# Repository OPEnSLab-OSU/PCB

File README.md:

# Project List
Opens Staff - Clone this repo and make a folder for your PCB. Once your PCB is added, place project links and update board file links here 

## [EAGLE Library Files](https://github.com/OPEnSLab-OSU/PCB/tree/master/OPEnS_Library)
Managed Libraries Folder *Coming Soon*

<!-- Copy an existing entry and add your project links directly below this comment -->
## [Sapflow](https://github.com/OPEnSLab-OSU/OPEnS-Lab-Home/wiki/Sap-Flow-Meter)

**New* V3 Board [Sapflow](https://github.com/OPEnSLab-OSU/PCB/tree/master/Sapflow)

## [Evaporometer](https://github.com/OPEnSLab-OSU/OPEnS-Lab-Home/wiki/Evaporometer)

INA125P Load Cell Amp [DevBoard](https://github.com/OPEnSLab-OSU/PCB/tree/master/Evaporometer_Lite/INA125P)

**New* Evaporometer V2 [V2.2 Board](https://github.com/OPEnSLab-OSU/PCB/tree/master/Evaporometer_Lite)

## [Hypnos](https://github.com/OPEnSLab-OSU/OPEnS-Hypnos)

**New* V3 Board [Hypnos 12V](https://github.com/OPEnSLab-OSU/PCB/tree/master/Hypnos)

## [PNNL Flux Tool](https://github.com/OPEnSLab-OSU/PNNLFluxV1)

Head [board](https://github.com/OPEnSLab-OSU/PCB/blob/master/PNNLFlux/Head-Board/head-board.brd),
[schematic](https://github.com/OPEnSLab-OSU/PCB/blob/master/PNNLFlux/Head-Board/head-board.sch)

Rod [board](https://github.com/OPEnSLab-OSU/PCB/blob/master/PNNLFlux/Rod-Board/rod-board.brd),
[schematic](https://github.com/OPEnSLab-OSU/PCB/blob/master/PNNLFlux/Rod-Board/rod-board.sch)

MS580302 [Pressure/EC sensor](https://github.com/OPEnSLab-OSU/PCB/tree/master/PNNLFlux/MS5803-02BA)

## [SmartRock](https://github.com/OPEnSLab-OSU/SmartRock)

MS580302 Pressure [MS5803](https://github.com/OPEnSLab-OSU/PCB/tree/master/SmartRock/MS5803), 
HydroPCB [HydroPCB](https://github.com/OPEnSLab-OSU/PCB/tree/master/SmartRock/HydroPCB)

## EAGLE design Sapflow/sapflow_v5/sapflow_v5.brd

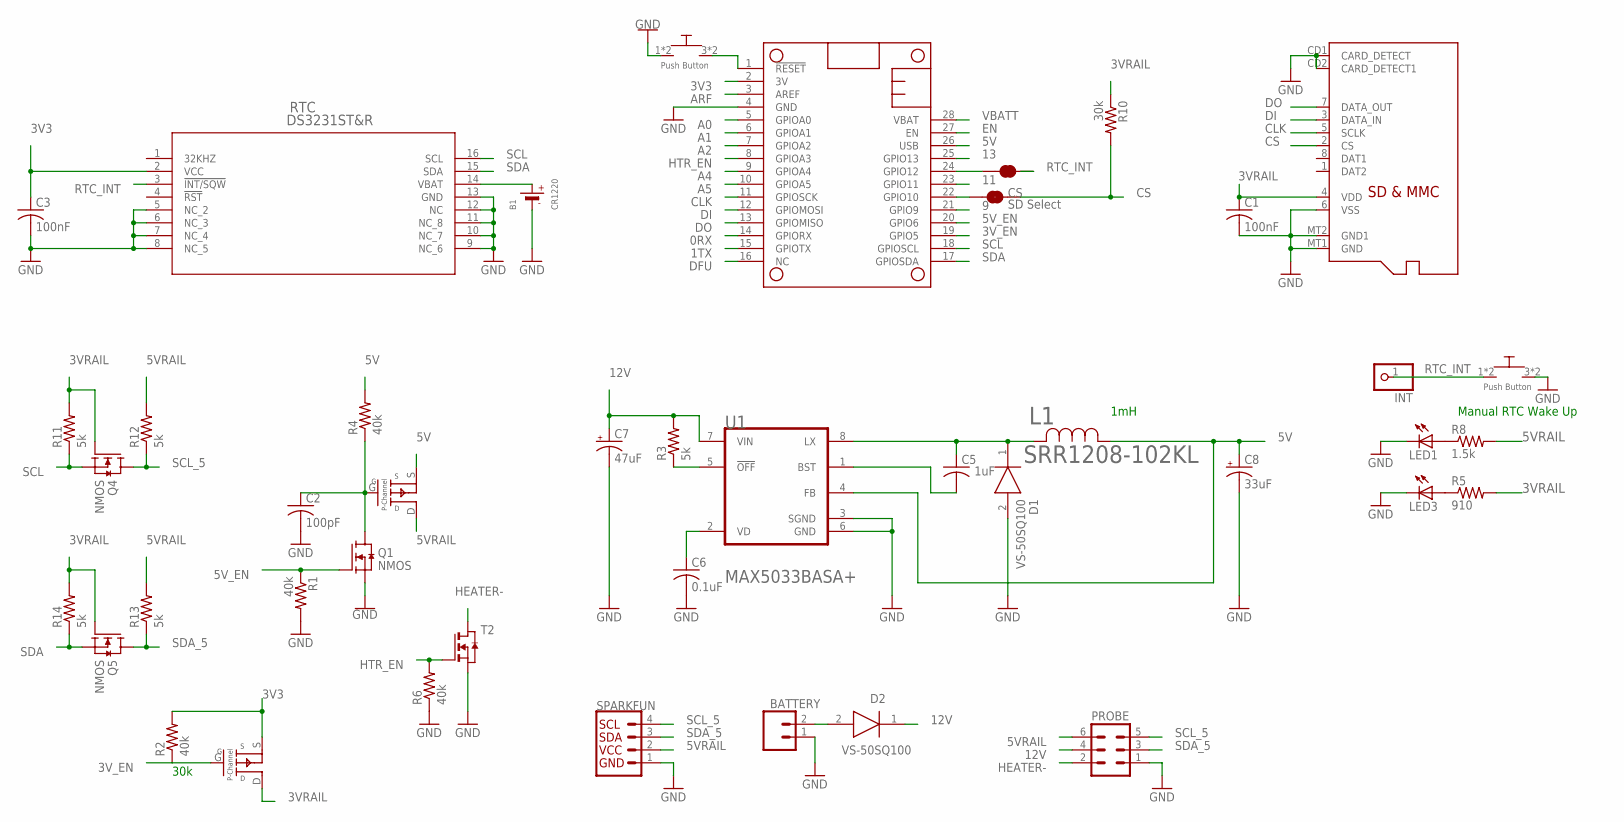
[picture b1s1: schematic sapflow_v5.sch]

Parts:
B1: CR1220
BATTERY: HIGHV-OUT; 1X02_NO_SILK
C1, C3: 100nF; C0805
C2: 100pF; C0805
C5: 1uF; C0805
C6: 0.1uF; C0805
C7: 47uF; D/7343-31R
C8: 33uF; D/7343-31R
CS: SD Select; SMT-JUMPER_2_NC_TRACE_SILK
D1, D2: VS-50SQ100; DIOAD1405W86L465D235
INT: PINHD-1X1CB; 1X01-CLEANBIG
L1: SRR1208-102KL; IND_BOURNS_SRR1208
LED1, LED3: RED; CHIPLED_0805
MICROSD: MICROSD
MS2: FEATHERWING
PMOS1, PMOS2: SSM3J3228R; SOT-23-3
PROBE: MA03-2
Q1, Q4, Q5: NMOS; SOT23-S
R1, R2, R4, R6: 40k; R0805
R3, R11, R12, R13, R14: 5k; R0805
R5: 910; R0805
R8: 1.5k; R0805
R10: 30k; R0805
RTC: DS3231ST&R; 21-0042B_16
RTC_INT: JUMPER-SMT_2_NC_TRACE_SILK; SMT-JUMPER_2_NC_TRACE_SILK
SPARKFUN: I2C_STANDARD_NO_SILK; 1X04_NO_SILK
T2: NMOSSOT223; SOT223
U1: MAXIM_MAX5033BASA+MAXIM_MAX5033BASA+_0_1; MAXIM_MAX5033BASA+_1
U$1, U$2: PUSH_BUTTON; PUSHBUTTON_SMD

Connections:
0RX: MS2.14 (GPIORX)
1TX: MS2.15 (GPIOTX)
3V3: C3.1, MS2.2 (3V), PMOS2.S, R2.2, RTC.2 (VCC)
3VRAIL: C1.1, MICROSD.4 (VDD), PMOS2.D, Q4.1 (G), Q5.1 (G), R5.2, R10.1, R11.2, R14.2
3V_EN: MS2.19 (GPIO5), PMOS2.G, R2.1
5V: C8.+, L1.1, MS2.26 (USB), PMOS1.S, R4.2, U1.4 (FB)
5VRAIL: PMOS1.D, PROBE.6, R8.2, R12.2, R13.2, SPARKFUN.2 (VCC)
5V_EN: MS2.20 (GPIO6), Q1.1 (G), R1.1
9: MS2.21 (GPIO9)
11: MS2.23 (GPIO11)
12V: C7.+, D2.1 (K), PROBE.4, R3.2, U1.7 (VIN)
13: MS2.25 (GPIO13)
A0: MS2.5 (GPIOA0)
A1: MS2.6 (GPIOA1)
A2: MS2.7 (GPIOA2)
A4: MS2.9 (GPIOA4)
A5: MS2.10 (GPIOA5)
ARF: MS2.3 (AREF)
CLK: MICROSD.5 (SCLK), MS2.11 (GPIOSCK)
CS: CS.2, MICROSD.2 (CS), R10.2
DFU: MS2.16 (NC)
DI: MICROSD.3 (DATA_IN), MS2.12 (GPIOMOSI)
DO: MICROSD.7 (DATA_OUT), MS2.13 (GPIOMISO)
EN: MS2.27 (EN)
GND: B1.-, BATTERY.1, C1.2, C2.2, C3.2, C6.2, C7.-, C8.-, D1.2 (A), LED1.C, LED3.C, MICROSD.6 (VSS), MICROSD.CD1 (CARD_DETECT), MICROSD.CD2 (CARD_DETECT1), MICROSD.MT1 (GND), MICROSD.MT2 (GND1), MS2.4 (GND), PROBE.1, Q1.2 (S), R1.2, R6.1, RTC.5 (NC_2), RTC.6 (NC_3), RTC.7 (NC_4), RTC.8 (NC_5), RTC.9 (NC_6), RTC.10 (NC_7), RTC.11 (NC_8), RTC.12 (NC), RTC.13 (GND), SPARKFUN.1 (GND), T2.3 (S), U1.3 (SGND), U1.6 (GND), U$1.1, U$1.2, U$2.3, U$2.4
HEATER-: PROBE.2, T2.2 (D), T2.4 (D)
HTR_EN: MS2.8 (GPIOA3), R6.2, T2.1 (G)
unnamed: MS2.1 (!RESET), U$1.3, U$1.4
unnamed: B1.+$1 (+), RTC.14 (VBAT)
unnamed: BATTERY.2, D2.2 (A)
unnamed: LED3.A, R5.1
unnamed: C6.1, U1.2 (VD)
unnamed: R3.1, U1.5 (!OFF!)
unnamed: C2.1, PMOS1.G, Q1.3 (D), R4.1
unnamed: CS.1, MS2.22 (GPIO10)
unnamed: LED1.A, R8.1
unnamed: MS2.24 (GPIO12), RTC_INT.1
unnamed: C5.2, U1.1 (BST)
unnamed: C5.1, D1.1 (K), L1.2, U1.8 (LX)
RTC_INT: INT.1, RTC.3 (!INT/SQW), RTC_INT.2, U$2.1, U$2.2
SCL: MS2.18 (GPIOSCL), Q4.2 (S), R11.1, RTC.16 (SCL)
SCL_5: PROBE.5, Q4.3 (D), R12.1, SPARKFUN.4 (SCL)
SDA: MS2.17 (GPIOSDA), Q5.2 (S), R14.1, RTC.15 (SDA)
SDA_5: PROBE.3, Q5.3 (D), R13.1, SPARKFUN.3 (SDA)
VBATT: MS2.28 (VBAT)

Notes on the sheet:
Manual RTC Wake Up
30k
1mH

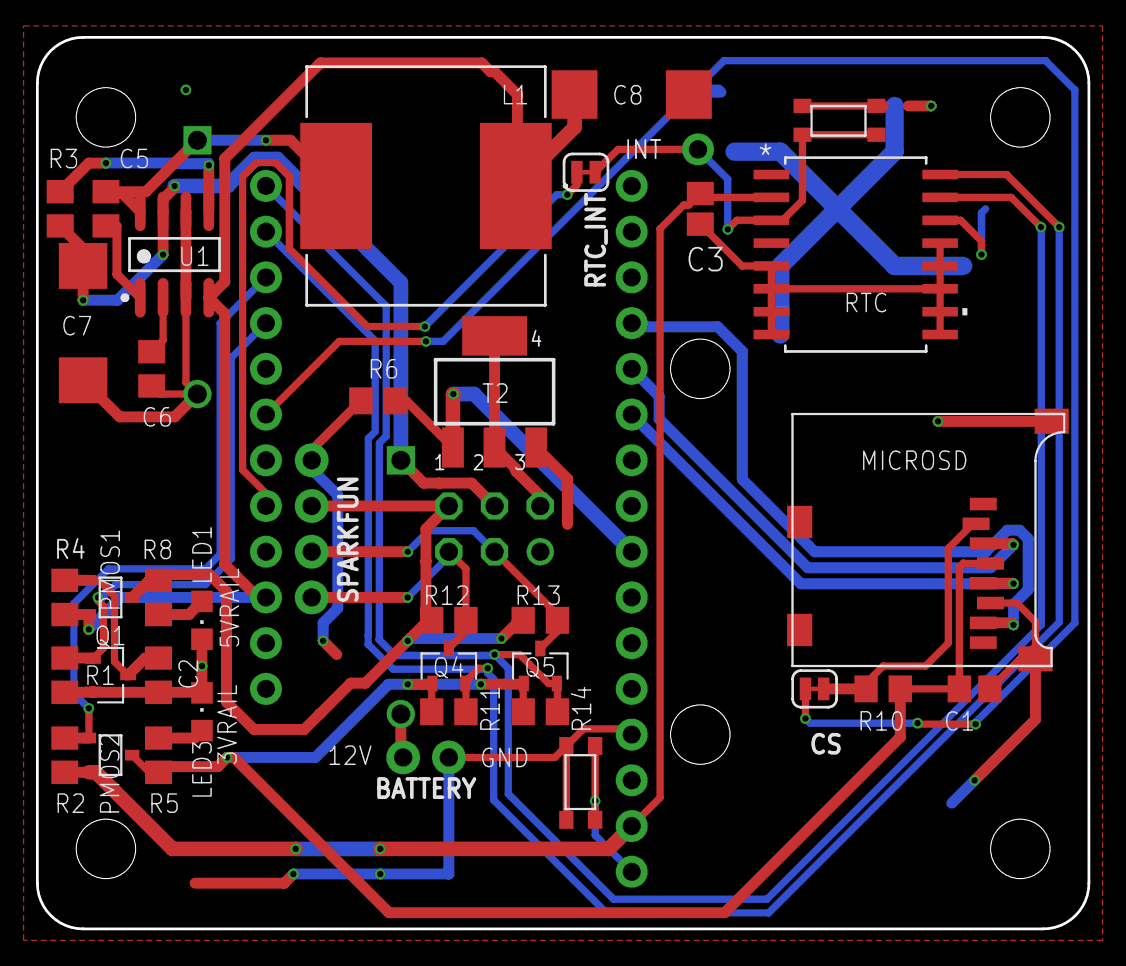
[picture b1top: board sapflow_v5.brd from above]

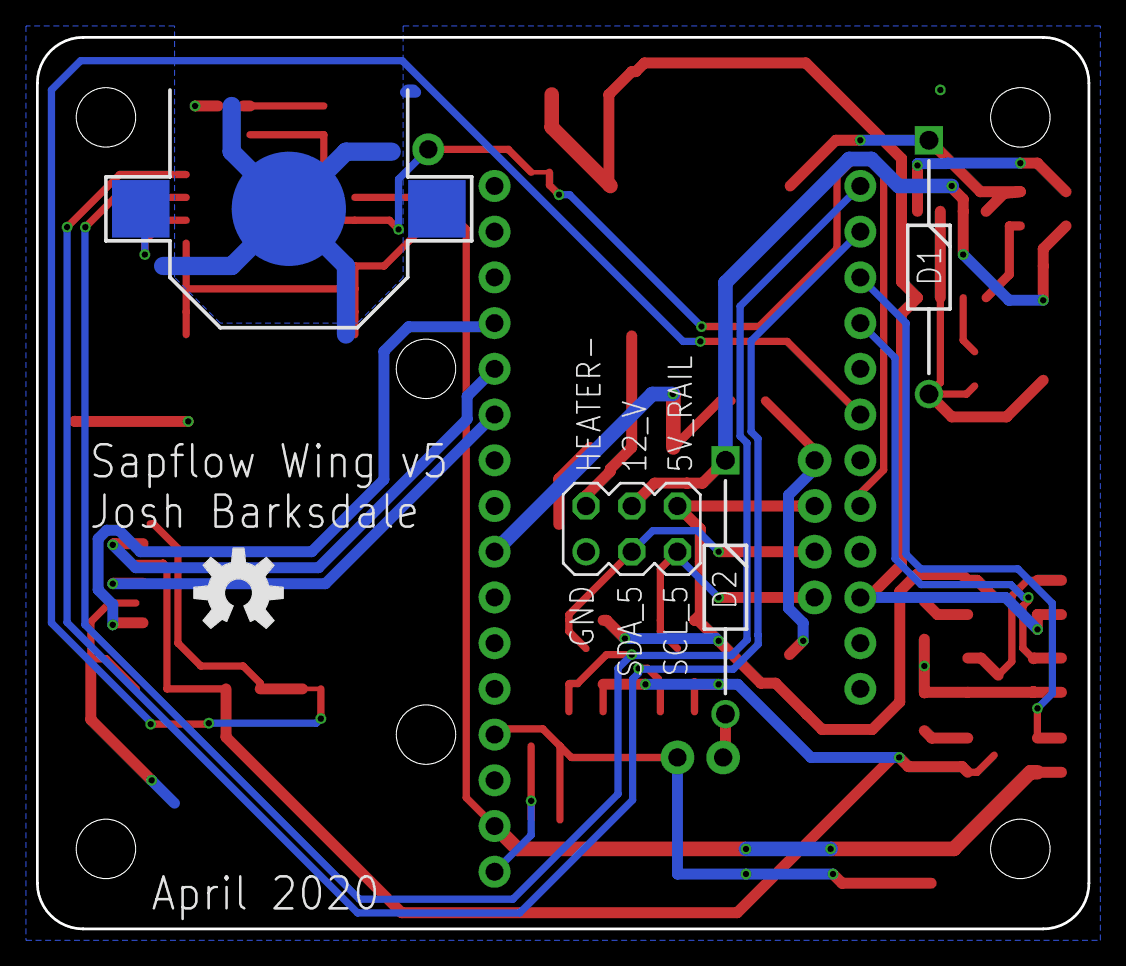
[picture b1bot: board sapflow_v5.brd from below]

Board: 2 copper layers, 58.4 x 49.5 mm, 50 parts (5 on the bottom side), 31 nets.

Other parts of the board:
H2, H4, H5, H6, H7, H8: STAND-OFF
LOGO1: OSHW-LOGOM; OSHW-LOGO-M

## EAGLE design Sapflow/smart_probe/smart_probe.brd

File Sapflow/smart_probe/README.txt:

This PCB attatches to the Sapflow project probe and makes it "smart".
It has a 3-channel ADC with analog lowpass filters in front of the inputs. 
It also has a differential I2C driver chip which can send I2C data from
the ADC over CAT V cables a couple meters long.

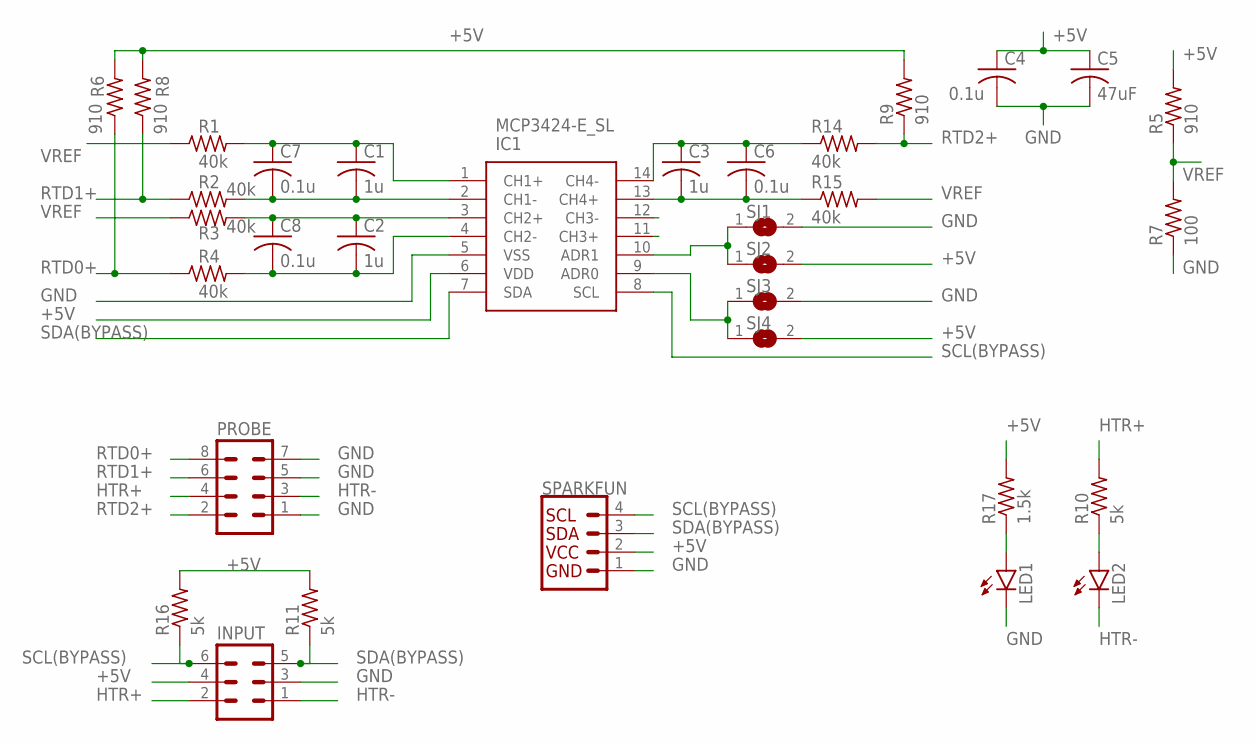
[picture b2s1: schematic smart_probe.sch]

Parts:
C1, C2, C3: 1u; C0805
C4, C6, C7, C8: 0.1u; C0805
C5: 47uF; C0805
IC1: MCP3424-E_SL; SOIC127P600X175-14N
INPUT: MA03-2
LED1, LED2: LEDCHIP-LED0805; CHIP-LED0805
PROBE: MA04-2
R1, R2, R3, R4, R14, R15: 40k; R0805
R5, R6, R8, R9: 910; R0805
R7: 100; R0805
R10, R11, R16: 5k; R0805
R17: 1.5k; R0805
SJ1, SJ2, SJ3, SJ4: SJ
SPARKFUN: I2C_STANDARD_NO_SILK; 1X04_NO_SILK

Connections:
+5V: C4.1, C5.1, IC1.6 (VDD), INPUT.4, R5.2, R6.2, R8.2, R9.2, R11.2, R16.2, R17.2, SJ2.2, SJ4.2, SPARKFUN.2 (VCC)
CH1+: C1.1, C7.1, IC1.1 (CH1+), R1.2
CH1-: C1.2, C7.2, IC1.2 (CH1-), R2.2
CH2+: C2.1, C8.1, IC1.3 (CH2+), R3.2
CH2-: C2.2, C8.2, IC1.4 (CH2-), R4.2
CH3+: IC1.11 (CH3+)
CH3-: IC1.12 (CH3-)
CH4+: C3.2, C6.2, IC1.13 (CH4+), R15.1
CH4-: C3.1, C6.1, IC1.14 (CH4-), R14.1
GND: C4.2, C5.2, IC1.5 (VSS), INPUT.3, LED1.C, PROBE.1, PROBE.5, PROBE.7, R7.1, SJ1.2, SJ3.2, SPARKFUN.1 (GND)
HTR+: INPUT.2, PROBE.4, R10.2
HTR-: INPUT.1, LED2.C, PROBE.3
unnamed: LED1.A, R17.1
unnamed: LED2.A, R10.1
unnamed: IC1.10 (ADR1), SJ1.1, SJ2.1
unnamed: IC1.9 (ADR0), SJ3.1, SJ4.1
RTD0+: PROBE.8, R4.1, R6.1
RTD1+: PROBE.6, R2.1, R8.1
RTD2+: PROBE.2, R9.1, R14.2
SCL(BYPASS): IC1.8 (SCL), INPUT.6, R16.1, SPARKFUN.4 (SCL)
SDA(BYPASS): IC1.7 (SDA), INPUT.5, R11.1, SPARKFUN.3 (SDA)
VREF: R1.1, R3.1, R5.1, R7.2, R15.2

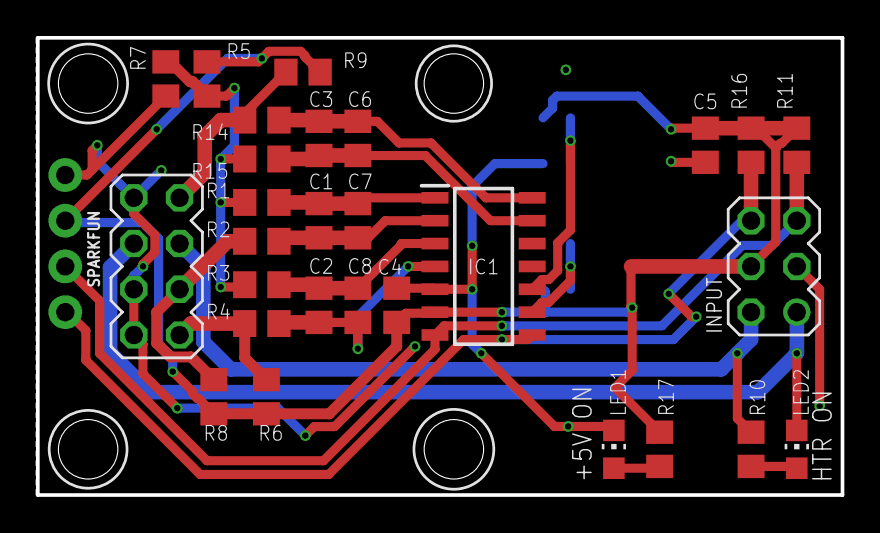
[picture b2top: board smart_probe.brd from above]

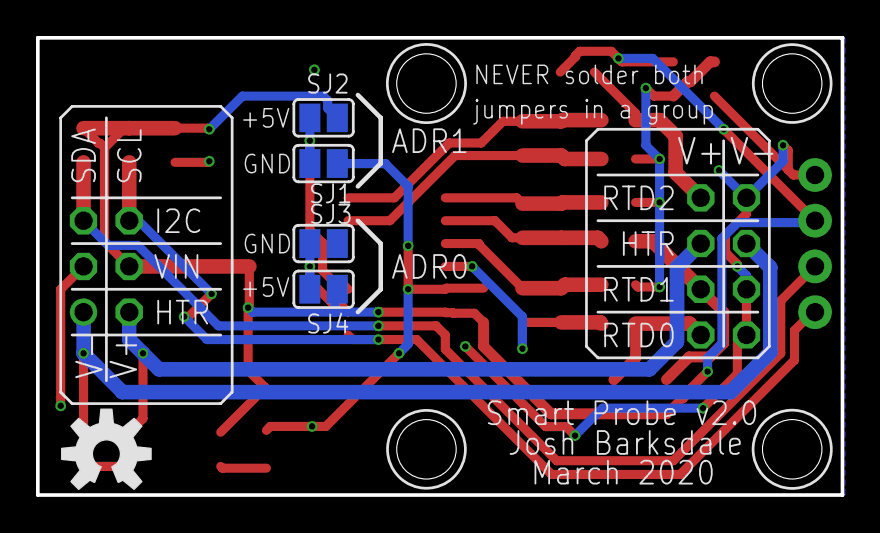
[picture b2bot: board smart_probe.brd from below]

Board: 2 copper layers, 44.7 x 25.4 mm, 38 parts (5 on the bottom side), 20 nets.

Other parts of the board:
H1, H2, H3, H4: STAND-OFF
LOGO1: OSHW-LOGOM; OSHW-LOGO-M

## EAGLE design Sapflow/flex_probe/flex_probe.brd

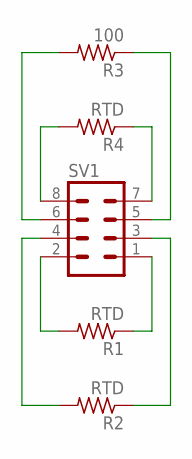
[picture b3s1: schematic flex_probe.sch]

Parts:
R1, R2, R4: RTD; R0603
R3: 100; R0603
SV1: MA04-2

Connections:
unnamed: R1.2, SV1.2
unnamed: R1.1, SV1.1
unnamed: R2.2, SV1.4
unnamed: R2.1, SV1.3
unnamed: R4.1, SV1.7
unnamed: R3.2, SV1.6
unnamed: R3.1, SV1.5
unnamed: R4.2, SV1.8

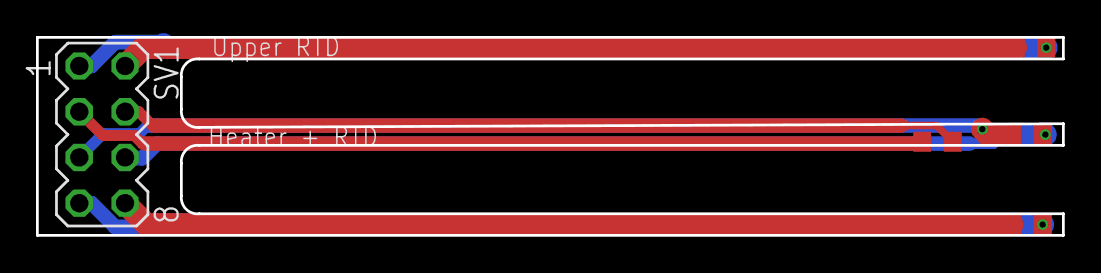
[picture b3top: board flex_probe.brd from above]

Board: 2 copper layers, 57.0 x 11.0 mm, 5 parts (0 on the bottom side), 8 nets.

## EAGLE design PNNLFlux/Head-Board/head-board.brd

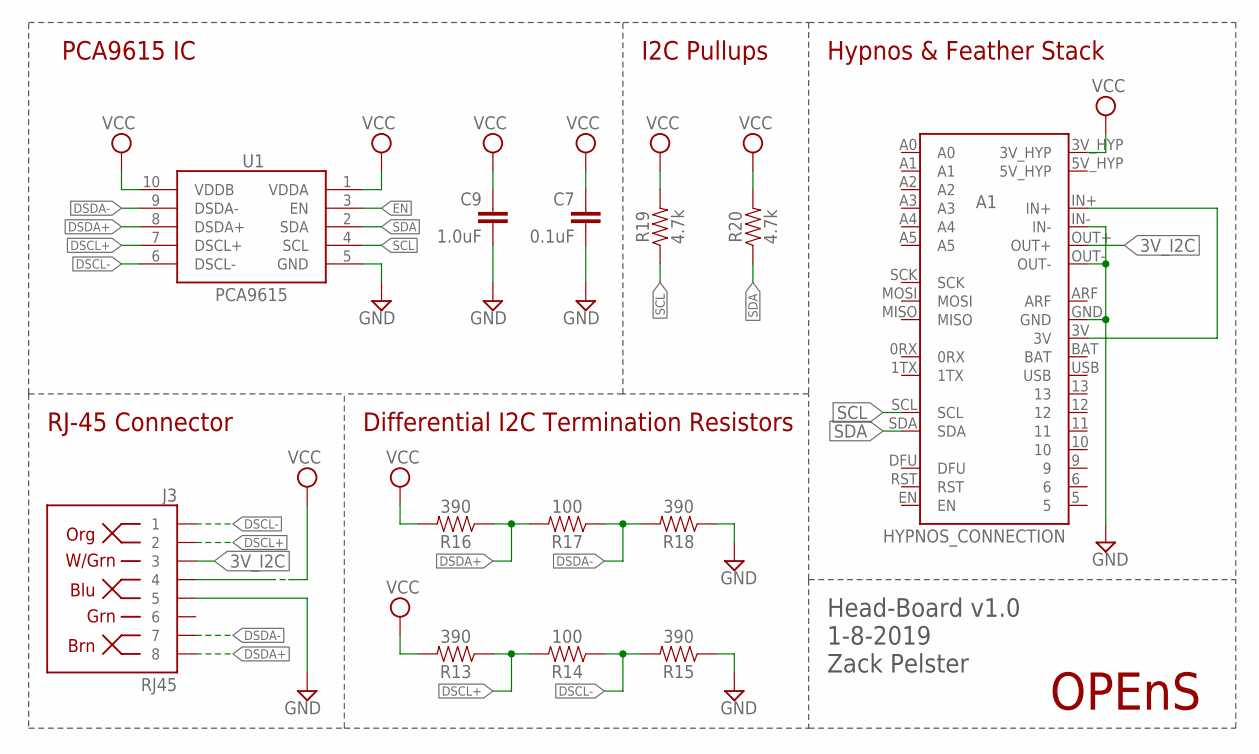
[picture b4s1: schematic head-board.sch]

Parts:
A1: HYPNOS_CONNECTION
C7: 0.1uF; 0603
C9: 1.0uF; 0603
J3: RJ45; RJ45-8
R13, R15, R16, R18: 390; 0603
R14, R17: 100; 0603
R19, R20: 4.7k; 0603
U1: PCA9615; TSSOP10
U$1: OPENS-LOGO

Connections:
3V_I2C: A1.OUT+, J3.3
BAT: A1.BAT
DSCL+: J3.2, R13.1, R14.2, U1.7 (DSCL+)
DSCL-: J3.1, R14.1, R15.2, U1.6 (DSCL-)
DSDA+: J3.8, R16.1, R17.2, U1.8 (DSDA+)
DSDA-: J3.7, R17.1, R18.2, U1.9 (DSDA-)
EN: U1.3 (EN)
GND: A1.GND, A1.IN-, A1.OUT-, C7.2, C9.2, J3.5, R15.1, R18.1, U1.5 (GND)
unnamed: A1.3V, A1.IN+
SCL: A1.SCL, R19.1, U1.4 (SCL)
SDA: A1.SDA, R20.1, U1.2 (SDA)
USB: A1.USB
VCC: A1.3V_HYP, C7.1, C9.1, J3.4, R13.2, R16.2, R19.2, R20.2, U1.1 (VDDA), U1.10 (VDDB)

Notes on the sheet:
PCA9615 IC
I2C Pullups
RJ-45 Connector
Differential I2C Termination Resistors
Head-Board v1.0 1-8-2019 Zack Pelster
Hypnos & Feather Stack

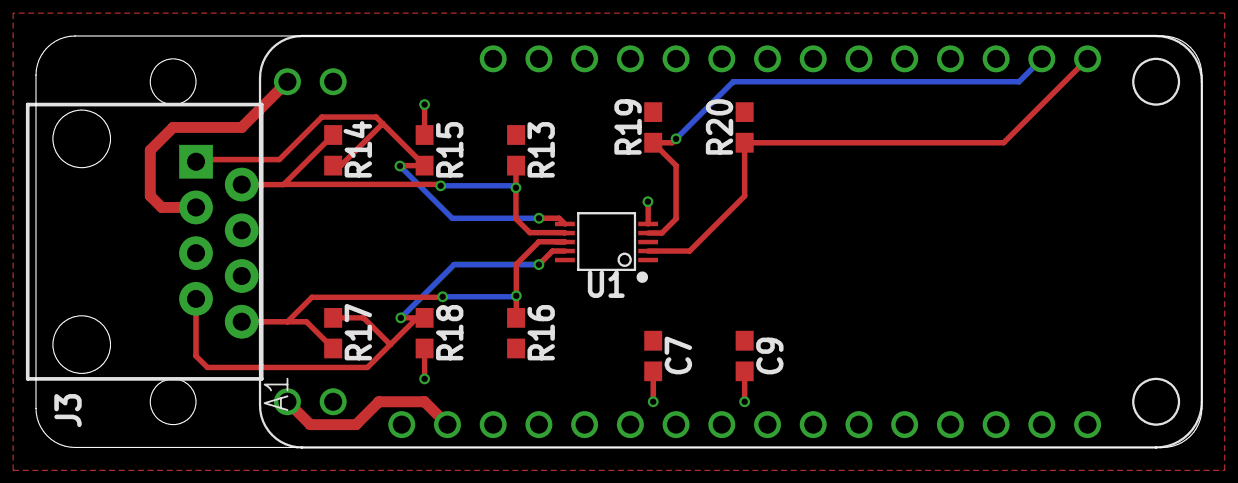
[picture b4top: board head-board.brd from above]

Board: 2 copper layers, 64.8 x 22.9 mm, 14 parts (1 on the bottom side), 10 nets.

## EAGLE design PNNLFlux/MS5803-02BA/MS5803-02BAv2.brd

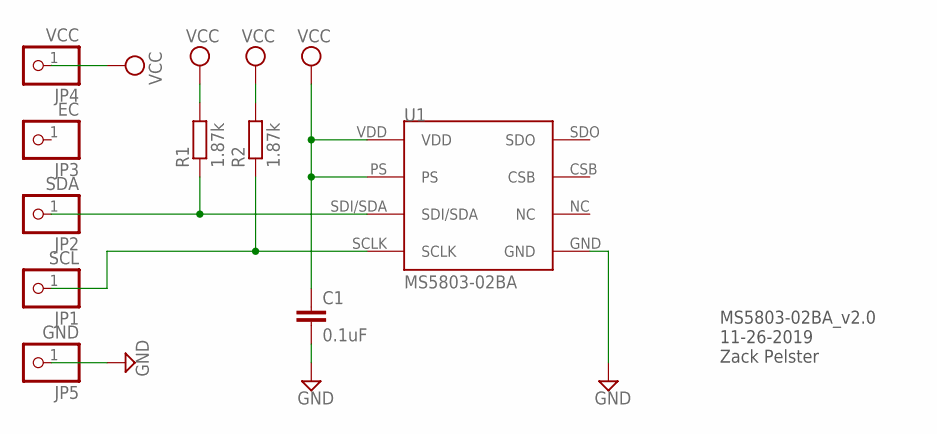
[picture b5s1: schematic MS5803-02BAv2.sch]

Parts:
C1: 0.1uF; C0805
JP1: SCL; 1X01
JP2: SDA; 1X01
JP3: EC; 1X01
JP4: VCC; 1X01
JP5: GND; 1X01
R1, R2: 1.87k; R0805
U1: MS5803-02BA

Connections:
GND: C1.2, JP5.1, U1.GND
unnamed: JP2.1, R1.1, U1.SDI/SDA
unnamed: JP1.1, R2.1, U1.SCLK
VCC: C1.1, JP4.1, R1.2, R2.2, U1.PS, U1.VDD

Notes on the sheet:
MS5803-02BA_v2.0 11-26-2019 Zack Pelster

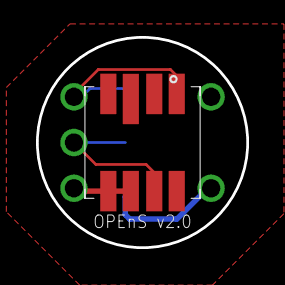
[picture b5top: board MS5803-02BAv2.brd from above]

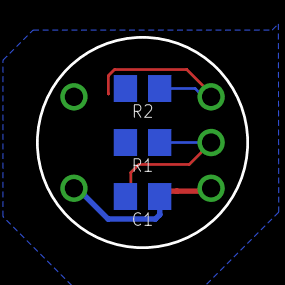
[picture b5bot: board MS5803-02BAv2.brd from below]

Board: 2 copper layers, 11.7 x 11.7 mm, 9 parts (3 on the bottom side), 4 nets.

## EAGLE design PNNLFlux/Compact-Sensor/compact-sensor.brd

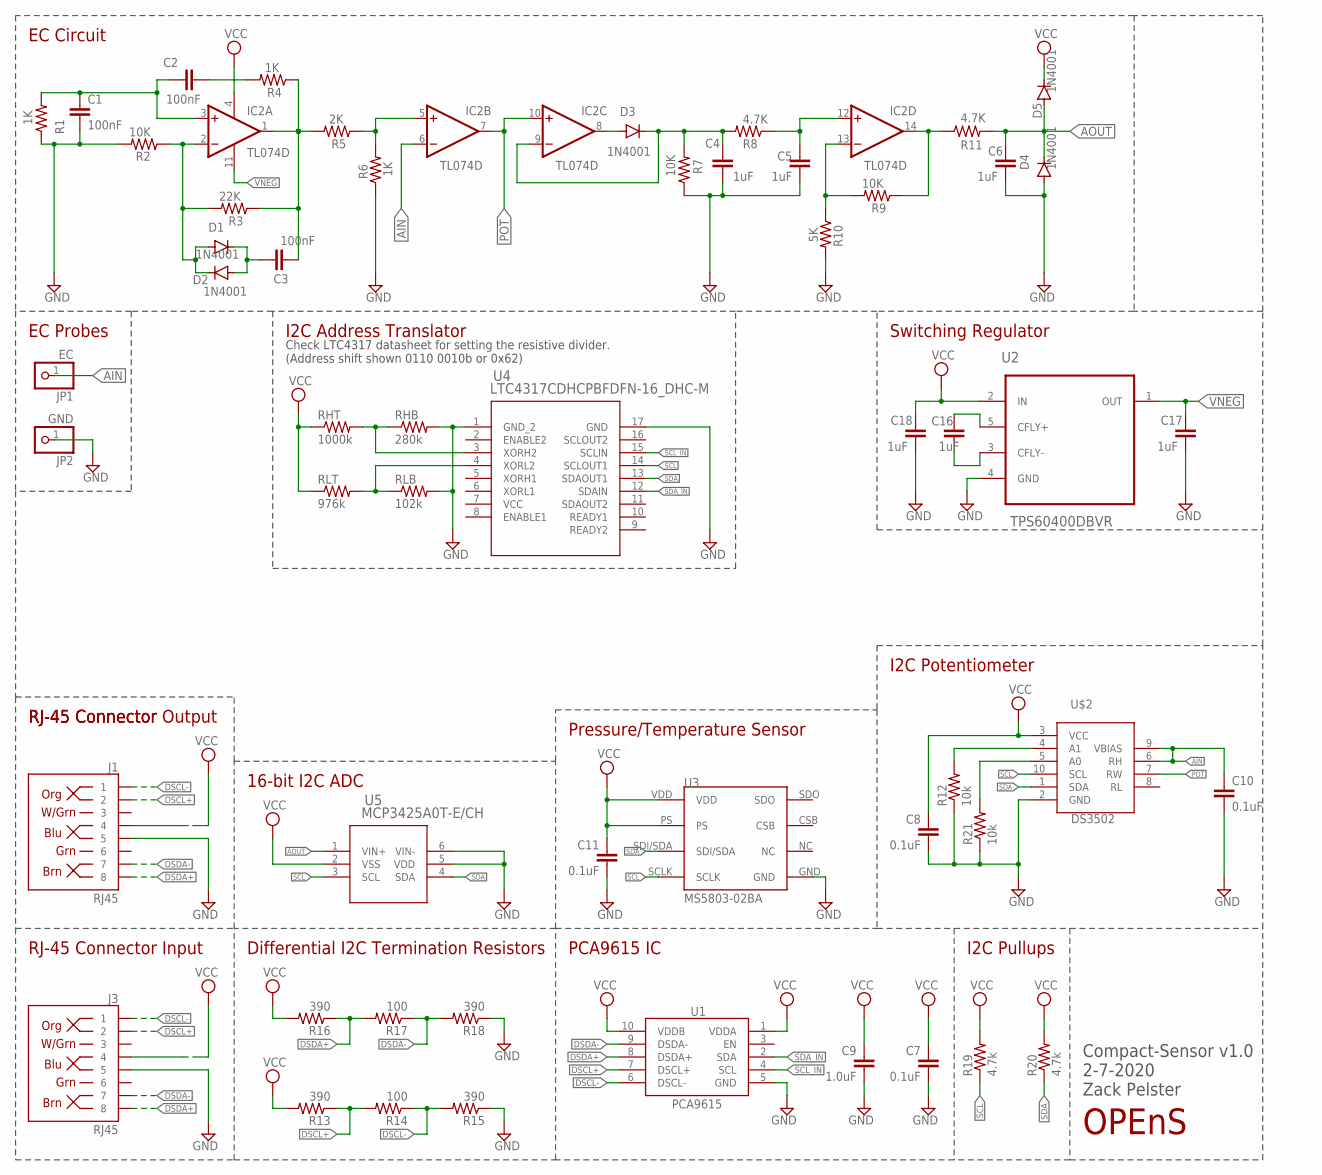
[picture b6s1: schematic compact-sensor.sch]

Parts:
C1, C2, C3: 100nF; C0603
C4, C5, C6, C16, C17, C18: 1uF; C0603
C7, C8, C10, C11: 0.1uF; C0603
C9: 1.0uF; C0603
D1, D2, D3, D4, D5: 1N4001; SOD123
IC2: TL074D; SO14
J1, J3: RJ45; RJ45-8
JP1: EC; 1X01
JP2: GND; 1X01
R1, R4, R6: 1K; R0603
R2, R7, R9: 10K; R0603
R3: 22K; R0603
R5: 2K; R0603
R8, R11: 4.7K; R0603
R10: 5K; R0603
R12, R21: 10k; R0603
R13, R15, R16, R18: 390; R0603
R14, R17: 100; R0603
R19, R20: 4.7k; R0603
RHB: 280k; R0603
RHT: 1000k; R0603
RLB: 102k; R0603
RLT: 976k; R0603
U1: PCA9615; TSSOP10
U2: TPS60400DBVR; SOT95P280X145-5N
U3: MS5803-02BA
U4: LTC4317CDHCPBFDFN-16_DHC-M; DFN-16_DHC-M
U5: MCP3425A0T-E/CH; SOT-23-6_MC
U$1: OPENS-LOGO
U$2: DS3502; MSOP10

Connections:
AIN: C10.1, IC2.6 (-IN), JP1.1, U$2.6 (RH), U$2.9 (VBIAS)
AOUT: C6.2, D4.C, D5.A, R11.2, U5.1 (VIN+)
DSCL+: J1.2, J3.2, R13.1, R14.2, U1.7 (DSCL+)
DSCL-: J1.1, J3.1, R14.1, R15.2, U1.6 (DSCL-)
DSDA+: J1.8, J3.8, R16.1, R17.2, U1.8 (DSDA+)
DSDA-: J1.7, J3.7, R17.1, R18.2, U1.9 (DSDA-)
GND: C1.2, C4.1, C5.1, C6.1, C7.2, C8.2, C9.2, C10.2, C11.2, C17.1, C18.1, D4.A, J1.5, J3.5, JP2.1, R1.1, R2.2, R6.1, R7.1, R10.2, R12.1, R15.1, R18.1, R21.1, RHB.2, RLB.2, U1.5 (GND), U2.4 (GND), U3.GND, U4.1 (GND_2), U4.17 (GND), U5.5 (VDD), U5.6 (VIN-), U$2.2 (GND)
unnamed: C1.1, C2.1, IC2.3 (+IN), R1.2
unnamed: C2.2, R4.2
unnamed: C3.2, IC2.1 (OUT), R3.1, R4.1, R5.2
unnamed: D1.A, D2.C, IC2.2 (-IN), R2.1, R3.2
unnamed: IC2.5 (+IN), R5.1, R6.2
unnamed: R12.2, U$2.4 (A1)
unnamed: R21.2, U$2.5 (A0)
unnamed: C3.1, D1.C, D2.A
unnamed: RHB.1, RHT.2, U4.3 (XORH2)
unnamed: C4.2, D3.C, IC2.9 (-IN), R7.2, R8.2
unnamed: D3.A, IC2.8 (OUT)
unnamed: C5.2, IC2.12 (+IN), R8.1
unnamed: IC2.13 (-IN), R9.2, R10.1
unnamed: RLB.1, RLT.2, U4.4 (XORL2)
unnamed: IC2.14 (OUT), R9.1, R11.1
unnamed: C16.2, U2.5 (CFLY+)
unnamed: C16.1, U2.3 (CFLY-)
POT: IC2.7 (OUT), IC2.10 (+IN), U$2.7 (RW)
SCL: R19.1, U3.SCLK, U4.14 (SCLOUT1), U5.3 (SCL), U$2.10 (SCL)
SCL_IN: U1.4 (SCL), U4.15 (SCLIN)
SDA: R20.1, U3.SDI/SDA, U4.13 (SDAOUT1), U5.4 (SDA), U$2.1 (SDA)
SDA_IN: U1.2 (SDA), U4.12 (SDAIN)
VCC: C7.1, C8.1, C9.1, C11.1, C18.2, D5.C, IC2.4 (V+), J1.4, J3.4, R13.2, R16.2, R19.2, R20.2, RHT.1, RLT.1, U1.1 (VDDA), U1.10 (VDDB), U2.2 (IN), U3.PS, U3.VDD, U4.7 (VCC), U$2.3 (VCC)
VNEG: C17.2, IC2.11 (V-), U2.1 (OUT)

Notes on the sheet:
PCA9615 IC
I2C Pullups
RJ-45 Connector Input
Differential I2C Termination Resistors
Switching Regulator
EC Circuit
Compact-Sensor v1.0 2-7-2020 Zack Pelster
I2C Potentiometer
Pressure/Temperature Sensor
16-bit I2C ADC
I2C Address Translator
Check LTC4317 datasheet for setting the resistive divider. (Address shift shown 0110 0010b or 0x62)
RJ-45 Connector
RJ-45 Connector Output
EC Probes

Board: 2 copper layers, 56 parts (28 on the bottom side), 31 nets, no tracks yet.

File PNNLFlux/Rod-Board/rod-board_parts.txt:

Partlist

Exported from rod-board.brd at 12/20/19 8:15 AM

EAGLE Version 9.5.1 Copyright (c) 1988-2019 Autodesk, Inc.

Assembly variant: 

Part     Value          Package          Library             Position (inch)       Orientation

A1       ADS1115        ADS1115          PNNL_Probe          (0.7 3.3)             R90
A2       TCA9548A       TCA9548A         PNNL_Probe          (0 4.45)              R0
A3       DS3502         DS3502           PNNL_Probe          (0.7 2.25)            R90
ACOUT    PTR1PAD1-13    P1-13            testpad             (0.6 1.2)             R0
AOUT     PTR1PAD1-13    P1-13            testpad             (0.6 2.1)             R0
C1       100nF          C1206            rcl                 (0.45 0.75)           R270
C2       100nF          C1206            rcl                 (0.6 1)               R90
C3       100nF          C1206            rcl                 (0.15 1.25)           R90
C4       1uF            C1206            rcl                 (0.3 1.65)            R270
C5       1uF            C1206            rcl                 (0.6 1.65)            R90
C6       1uF            C1206            rcl                 (0.6 1.9)             R90
C7       0.1uF          0603             SparkFun-Capacitors (0.25 5.6)            R270
C9       1.0uF          0603             SparkFun-Capacitors (0.45 5.6)            R270
C16      1uF            C1206            rcl                 (0.15 2.4)            R270
C17      1uF            C1206            rcl                 (0.3 2.4)             R270
C18      1uF            C1206            rcl                 (0.45 2.4)            R270
D1       1N4001         D-5              diode               (0.3 1)               R270
D2       1N4001         D-5              diode               (0.15 1)              R90
D3       1N4001         D-5              diode               (0.35 1.45)           R0
D4       1N4001         D-5              diode               (0.45 2.15)           R90
D5       1N4001         D-5              diode               (0.3 2.15)            R270
IC1      CD4051BE       CD4051BE         PNNL_Probe          (0.15 3.45)           MR90
IC2      TL074P         DIL14            linear              (0.35 3)              MR90
IC3      MCP23008       MCP23008         PNNL_Probe          (0.1 4.25)            MR90
J3       RJ45           RJ45-8           SparkFun-Connectors (0.35 6.1)            R180
JP1                     1X03             pinhead             (0.2 0.1)             R0
JP2                     1X03             pinhead             (0.5 0.1)             R0
JP3                     1X03             pinhead             (0.2 0.3)             R0
JP4                     1X03             pinhead             (0.5 0.3)             R0
JP5                     1X03             pinhead             (0.2 0.5)             R0
JP6                     1X02             pinhead             (0.55 0.5)            R0
PIN6     PTR1PAD1-13    P1-13            testpad             (0.6 3.2)             MR0
PIN7     PTR1PAD1-13    P1-13            testpad             (0.1 3.1)             MR0
PIN12    PTR1PAD1-13    P1-13            testpad             (0.6 1.45)            R0
R1       1K             R1206            rcl                 (0.6 0.75)            R90
R2       10K            R1206            rcl                 (0.3 0.75)            R270
R3       22K            R1206            rcl                 (0.15 0.75)           R90
R4       1K             R1206            rcl                 (0.45 1)              R90
R5       2K             R1206            rcl                 (0.3 1.25)            R90
R6       1K             R1206            rcl                 (0.45 1.25)           R270
R7       10K            R1206            rcl                 (0.15 1.65)           R270
R8       4.7K           R1206            rcl                 (0.45 1.65)           R270
R9       10K            R1206            rcl                 (0.3 1.9)             R90
R10      5K             R1206            rcl                 (0.15 1.9)            R270
R11      4.7K           R1206            rcl                 (0.45 1.9)            R90
R13      390            0603             SparkFun-Resistors  (0.55 5.6)            R90
R14      100            0603             SparkFun-Resistors  (0.55 5.45)           R90
R15      390            0603             SparkFun-Resistors  (0.55 5.3)            R90
R16      390            0603             SparkFun-Resistors  (0.15 5.6)            R90
R17      100            0603             SparkFun-Resistors  (0.15 5.45)           R90
R18      390            0603             SparkFun-Resistors  (0.15 5.3)            R90
R19      4.7k           0603             SparkFun-Resistors  (0.25 5.2)            R0
R20      4.7k           0603             SparkFun-Resistors  (0.45 5.2)            R180
U1       PCA9615        TSSOP10          SparkFun-IC-Comms   (0.35 5.4)            R0
U2       TPS60400DBVR   SOT95P280X145-5N TPS60400DBVR        (0.1 2.15)            R90
VCC1     PTR1PAD1-13    P1-13            testpad             (0.6 2.35)            MR270
VNEG1    PTR1PAD1-13    P1-13            testpad             (0.1 3)               MR0
WEIN     PTR1PAD1-13    P1-13            testpad             (0.15 1.45)           R0

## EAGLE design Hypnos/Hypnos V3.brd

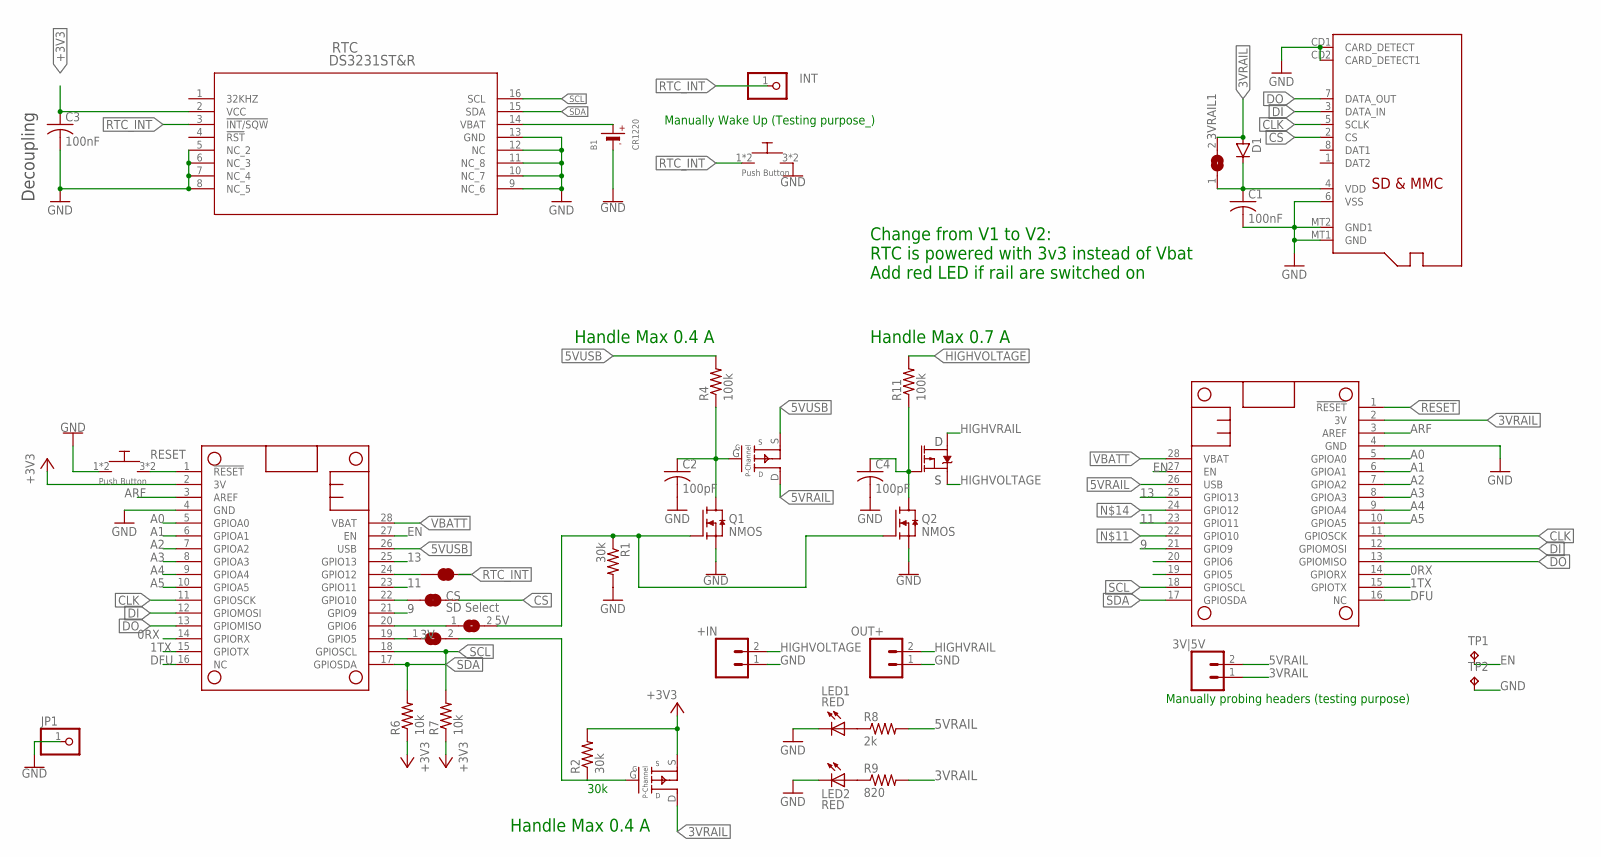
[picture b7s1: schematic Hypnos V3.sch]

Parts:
3V, 3VRAIL1, 5V: SJ
3V|5V: CONN_021X02_NO_SILK; 1X02_NO_SILK
+IN: HIGHV-IN; 1X02_NO_SILK
B1: CR1220
C1, C3: 100nF; C1206
C2, C4: 100pF; C0805
CS: SD Select; SMT-JUMPER_2_NC_TRACE_SILK
D1: D-SOD123; SOD123
INT: PINHD-1X1CB; 1X01-CLEANBIG
JP1: PINHD-1X1CB; 1X01-CLEANBIG
LED1, LED2: RED; CHIPLED_0805
MICROSD: MICROSD
MS1, MS2: FEATHERWING
OUT+: HIGHV-OUT; 1X02_NO_SILK
PMOS1, PMOS2: SSM3J3228R; SOT-23-3
PMOS3: P-MOSFET; SOT23-6
Q1, Q2: NMOS; SOT23-S
R1, R2: 30k; RES_1206
R4, R11: 100k; RES_1206
R6, R7: 10k; RES_1206
R8: 2k; RES_1206
R9: 820; RES_1206
RTC: DS3231ST&R; 21-0042B_16
RTC_INT: JUMPER-SMT_2_NC_TRACE_SILK; SMT-JUMPER_2_NC_TRACE_SILK
TP1, TP2: TPTP16R; TP16R
U$1, U$2: PUSH_BUTTON; PUSHBUTTON_SMD

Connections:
0RX: MS1.14 (GPIORX), MS2.14 (GPIORX)
1TX: MS1.15 (GPIOTX), MS2.15 (GPIOTX)
3VRAIL: 3VRAIL1.2, 3V|5V.1, D1.2 (A), MS1.2 (3V), PMOS2.D, R9.2
5VRAIL: 3V|5V.2, MS1.26 (USB), PMOS1.D, R8.2
5VUSB: MS2.26 (USB), PMOS1.S, R4.2
9: MS1.21 (GPIO9), MS2.21 (GPIO9)
11: MS1.23 (GPIO11), MS2.23 (GPIO11)
13: MS1.25 (GPIO13), MS2.25 (GPIO13)
+3V3: C3.1, MS2.2 (3V), PMOS2.S, R2.2, R6.1, R7.1, RTC.2 (VCC)
A0: MS1.5 (GPIOA0), MS2.5 (GPIOA0)
A1: MS1.6 (GPIOA1), MS2.6 (GPIOA1)
A2: MS1.7 (GPIOA2), MS2.7 (GPIOA2)
A3: MS1.8 (GPIOA3), MS2.8 (GPIOA3)
A4: MS1.9 (GPIOA4), MS2.9 (GPIOA4)
A5: MS1.10 (GPIOA5), MS2.10 (GPIOA5)
ARF: MS1.3 (AREF), MS2.3 (AREF)
CLK: MICROSD.5 (SCLK), MS1.11 (GPIOSCK), MS2.11 (GPIOSCK)
CS: CS.2, MICROSD.2 (CS)
DFU: MS1.16 (NC), MS2.16 (NC)
DI: MICROSD.3 (DATA_IN), MS1.12 (GPIOMOSI), MS2.12 (GPIOMOSI)
DO: MICROSD.7 (DATA_OUT), MS1.13 (GPIOMISO), MS2.13 (GPIOMISO)
EN: MS1.27 (EN), MS2.27 (EN), TP1.TP
GND: +IN.1, B1.-, C1.2, C2.2, C3.2, C4.2, JP1.1, LED1.C, LED2.C, MICROSD.6 (VSS), MICROSD.CD1 (CARD_DETECT), MICROSD.CD2 (CARD_DETECT1), MICROSD.MT1 (GND), MICROSD.MT2 (GND1), MS1.4 (GND), MS2.4 (GND), OUT+.1, Q1.2 (S), Q2.2 (S), R1.2, RTC.5 (NC_2), RTC.6 (NC_3), RTC.7 (NC_4), RTC.8 (NC_5), RTC.9 (NC_6), RTC.10 (NC_7), RTC.11 (NC_8), RTC.12 (NC), RTC.13 (GND), TP2.TP, U$1.1, U$1.2, U$2.3, U$2.4
HIGHVOLTAGE: +IN.2, PMOS3.4 (S), R11.2
HIGHVRAIL: OUT+.2, PMOS3.1 (D), PMOS3.2 (D), PMOS3.5 (D), PMOS3.6 (D)
unnamed: 5V.1, MS2.20 (GPIO6)
unnamed: B1.+$1 (+), RTC.14 (VBAT)
unnamed: 3V.1, MS2.19 (GPIO5)
unnamed: 5V.2, Q1.1 (G), Q2.1 (G), R1.1
unnamed: 3V.2, PMOS2.G, R2.1
unnamed: C2.1, PMOS1.G, Q1.3 (D), R4.1
unnamed: CS.1, MS1.22 (GPIO10), MS2.22 (GPIO10)
unnamed: LED1.A, R8.1
unnamed: LED2.A, R9.1
unnamed: MS1.24 (GPIO12), MS2.24 (GPIO12), RTC_INT.1
unnamed: C4.1, PMOS3.3 (G), Q2.3 (D), R11.1
RESET: MS1.1 (!RESET), MS2.1 (!RESET), U$1.3, U$1.4
RTC_INT: INT.1, RTC.3 (!INT/SQW), RTC_INT.2, U$2.1, U$2.2
SCL: MS1.18 (GPIOSCL), MS2.18 (GPIOSCL), R7.2, RTC.16 (SCL)
SDA: MS1.17 (GPIOSDA), MS2.17 (GPIOSDA), R6.2, RTC.15 (SDA)
VBATT: MS1.28 (VBAT), MS2.28 (VBAT)
VDD: 3VRAIL1.1, C1.1, D1.1 (C), MICROSD.4 (VDD)

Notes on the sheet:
Decoupling
Manually Wake Up (Testing purpose_)
Manually probing headers (testing purpose)
30k
Change from V1 to V2: RTC is powered with 3v3 instead of Vbat Add red LED if rail are switched on
Handle Max 0.7 A
Handle Max 0.4 A

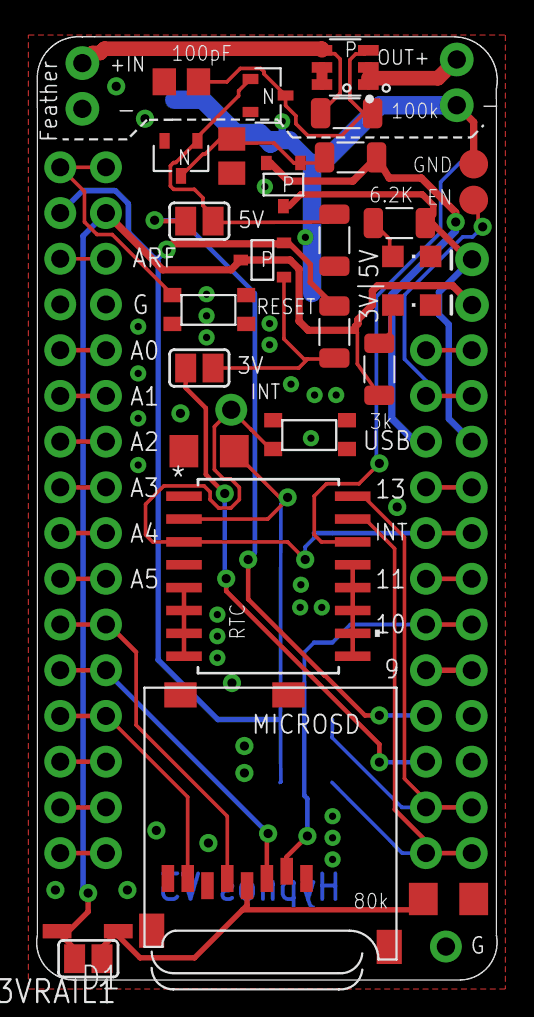
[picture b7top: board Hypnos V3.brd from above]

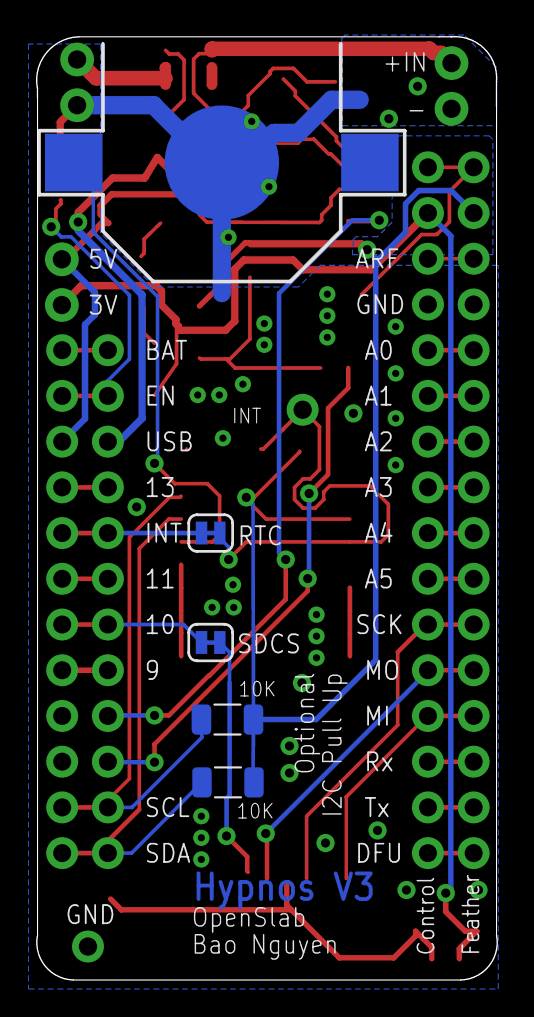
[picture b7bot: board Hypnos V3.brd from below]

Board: 2 copper layers, 25.6 x 52.4 mm, 39 parts (6 on the bottom side), 42 nets.

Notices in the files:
parts and their libraries:
SparkFun-PowerSymbols: Licensing: Creative Commons ShareAlike 4.0 International - https://creativecommons.org/licenses/by-sa/4.0
microbuilder: This work is placed in the public domain, and may be freely used for commercial and non-commercial work with the following conditions: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
